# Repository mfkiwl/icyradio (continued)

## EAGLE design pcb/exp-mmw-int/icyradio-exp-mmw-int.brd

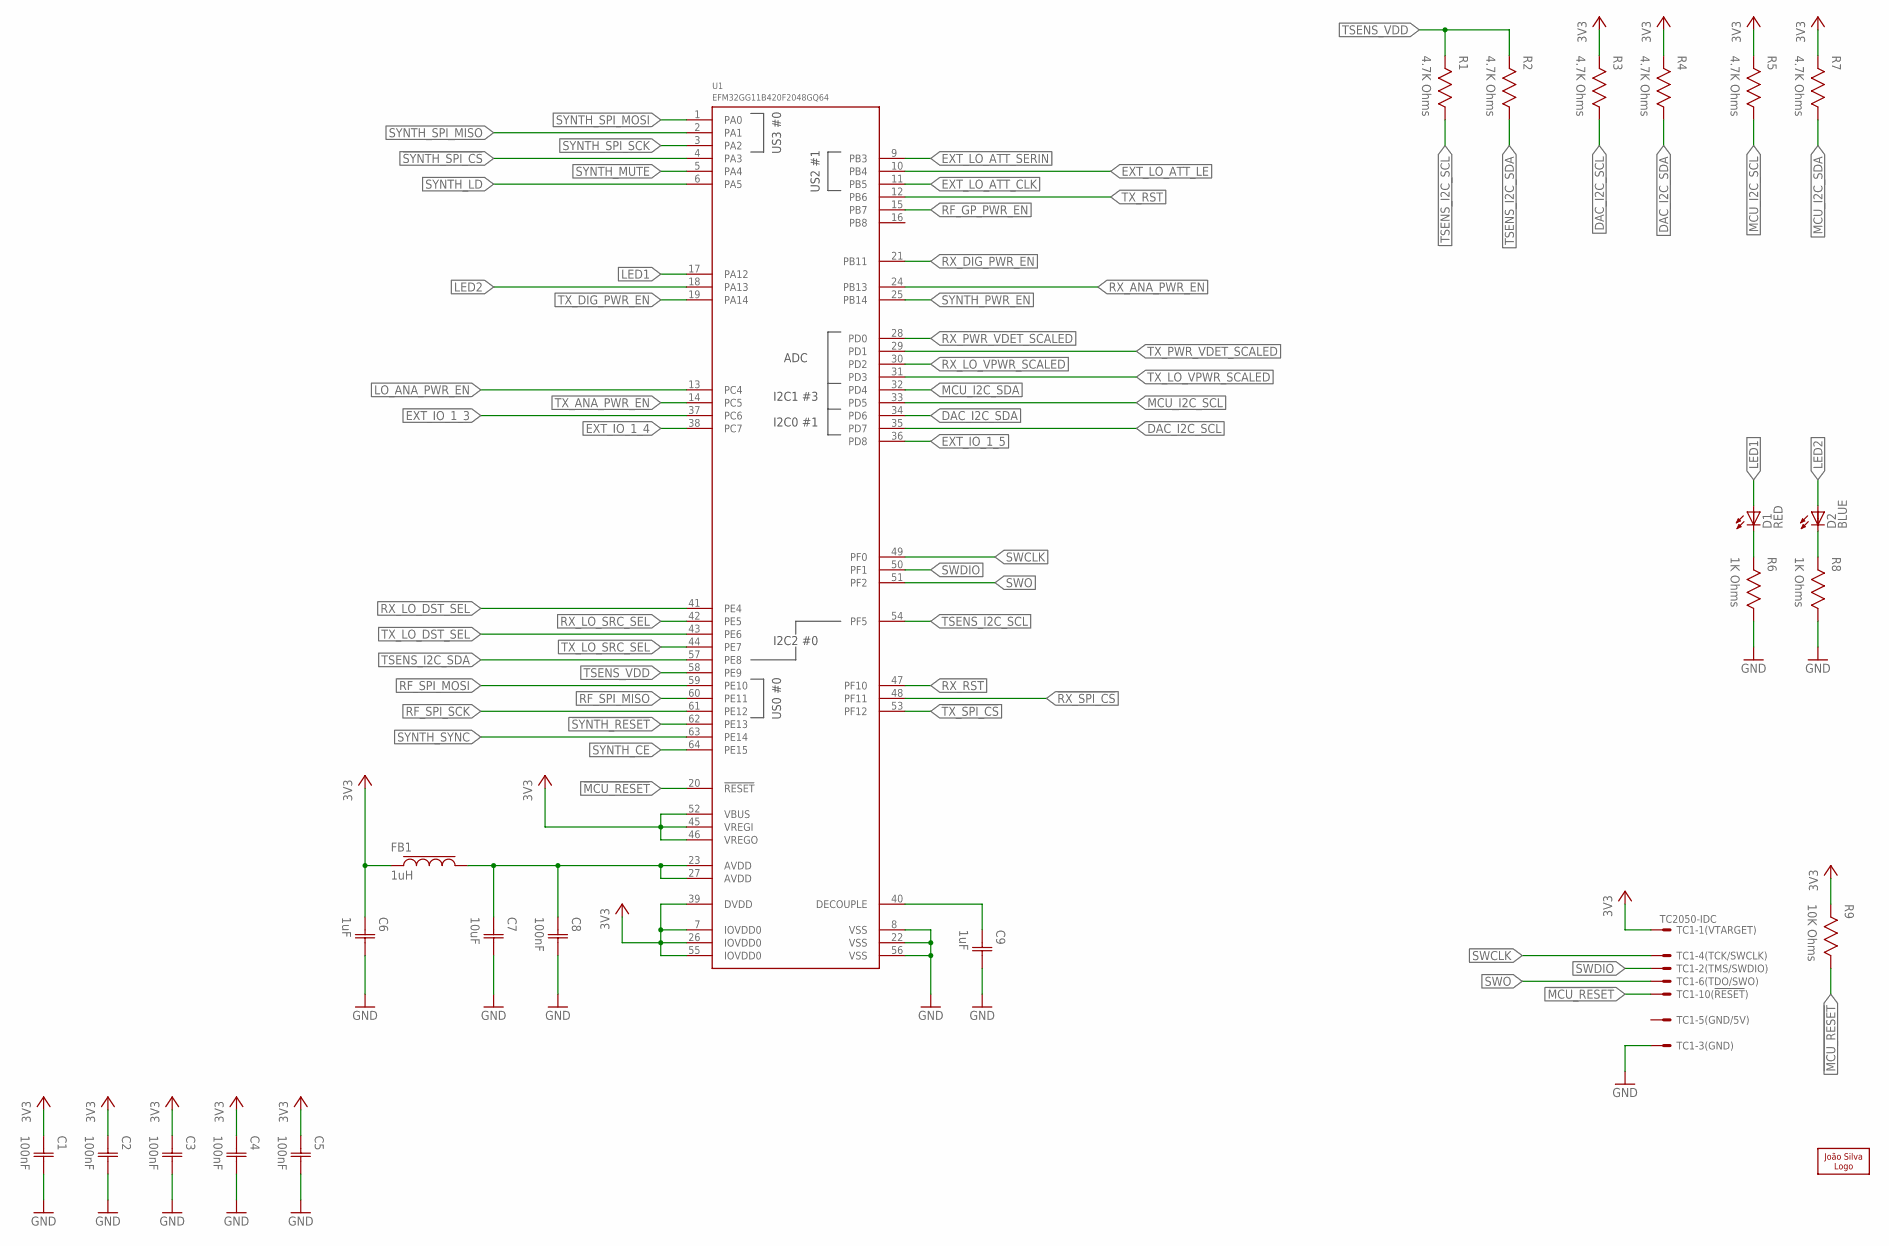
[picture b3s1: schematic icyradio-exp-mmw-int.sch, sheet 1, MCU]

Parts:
C1, C2, C3, C4, C5, C8: 100nF; CAP0402
C6, C9: 1uF; CAP0402
C7: 10uF; CAP0402
D1, D2: LED0603; 0603
FB1: 1uH; IND0603
LOGO1: JSILVA-5MM; JSILVA_5MM
R1, R2, R3, R4, R5, R7: 4.7K Ohms; RES0402
R6, R8: 1K Ohms; RES0402
R9: 10K Ohms; RES0402
TC1: TC2050-IDC
U1: EFM32GG11B420F2048GQ64; QFP64

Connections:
3V3: C1.1 (C1), C2.1 (C1), C3.1 (C1), C4.1 (C1), C5.1 (C1), C6.1 (C1), FB1.1, R3.2, R4.2, R5.2, R7.2, R9.2, TC1.1, U1.7 (IOVDD0), U1.26 (IOVDD0), U1.39 (DVDD), U1.45 (VREGI), U1.46 (VREGO), U1.52 (VBUS), U1.55 (IOVDD0); also elsewhere on the board
!MCU_RESET: R9.1, TC1.10, U1.20 (!RESET)
!RX_SPI_CS: U1.48 (PF11); also elsewhere on the board
!SYNTH_RESET: U1.62 (PE13); also elsewhere on the board
!SYNTH_SPI_CS: U1.4 (PA3); also elsewhere on the board
!TX_SPI_CS: U1.53 (PF12); also elsewhere on the board
DAC_I2C_SCL: R3.1, U1.35 (PD7); also elsewhere on the board
DAC_I2C_SDA: R4.1, U1.34 (PD6); also elsewhere on the board
EXT_IO_1_3: U1.37 (PC6); also elsewhere on the board
EXT_IO_1_4: U1.38 (PC7); also elsewhere on the board
EXT_IO_1_5: U1.36 (PD8); also elsewhere on the board
EXT_LO_ATT_CLK: U1.11 (PB5); also elsewhere on the board
EXT_LO_ATT_LE: U1.10 (PB4); also elsewhere on the board
EXT_LO_ATT_SERIN: U1.9 (PB3); also elsewhere on the board
GND: C1.2 (C2), C2.2 (C2), C3.2 (C2), C4.2 (C2), C5.2 (C2), C6.2 (C2), C7.2 (C2), C8.2 (C2), C9.2 (C2), R6.1, R8.1, TC1.3, U1.8 (VSS), U1.22 (VSS), U1.56 (VSS); also elsewhere on the board
LED1: D1.A, U1.17 (PA12)
LED2: D2.A, U1.18 (PA13)
LO_ANA_PWR_EN: U1.13 (PC4); also elsewhere on the board
MCU_AVDD: C7.1 (C1), C8.1 (C1), FB1.2, U1.23 (AVDD), U1.27 (AVDD)
MCU_I2C_SCL: R5.1, U1.33 (PD5); also elsewhere on the board
MCU_I2C_SDA: R7.1, U1.32 (PD4); also elsewhere on the board
unnamed: C9.1 (C1), U1.40 (DECOUPLE)
unnamed: D1.C, R6.2
unnamed: D2.C, R8.2
RF_GP_PWR_EN: U1.15 (PB7); also elsewhere on the board
RF_SPI_MISO: U1.60 (PE11); also elsewhere on the board
RF_SPI_MOSI: U1.59 (PE10); also elsewhere on the board
RF_SPI_SCK: U1.61 (PE12); also elsewhere on the board
RX_ANA_PWR_EN: U1.24 (PB13); also elsewhere on the board
RX_DIG_PWR_EN: U1.21 (PB11); also elsewhere on the board
RX_LO_DST_SEL: U1.41 (PE4); also elsewhere on the board
RX_LO_SRC_SEL: U1.42 (PE5); also elsewhere on the board
RX_LO_VPWR_SCALED: U1.30 (PD2); also elsewhere on the board
RX_PWR_VDET_SCALED: U1.28 (PD0); also elsewhere on the board
RX_RST: U1.47 (PF10); also elsewhere on the board
SWCLK: TC1.4, U1.49 (PF0)
SWDIO: TC1.2, U1.50 (PF1)
SWO: TC1.6, U1.51 (PF2)
SYNTH_CE: U1.64 (PE15); also elsewhere on the board
SYNTH_LD: U1.6 (PA5); also elsewhere on the board
SYNTH_MUTE: U1.5 (PA4); also elsewhere on the board
SYNTH_PWR_EN: U1.25 (PB14); also elsewhere on the board
SYNTH_SPI_MISO: U1.2 (PA1); also elsewhere on the board
SYNTH_SPI_MOSI: U1.1 (PA0); also elsewhere on the board
SYNTH_SPI_SCK: U1.3 (PA2); also elsewhere on the board
SYNTH_SYNC: U1.63 (PE14); also elsewhere on the board
TSENS_I2C_SCL: R1.1, U1.54 (PF5); also elsewhere on the board
TSENS_I2C_SDA: R2.1, U1.57 (PE8); also elsewhere on the board
TSENS_VDD: R1.2, R2.2, U1.58 (PE9); also elsewhere on the board
TX_ANA_PWR_EN: U1.14 (PC5); also elsewhere on the board
TX_DIG_PWR_EN: U1.19 (PA14); also elsewhere on the board
TX_LO_DST_SEL: U1.43 (PE6); also elsewhere on the board
TX_LO_SRC_SEL: U1.44 (PE7); also elsewhere on the board
TX_LO_VPWR_SCALED: U1.31 (PD3); also elsewhere on the board
TX_PWR_VDET_SCALED: U1.29 (PD1); also elsewhere on the board
TX_RST: U1.12 (PB6); also elsewhere on the board

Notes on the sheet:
US0 #0
I2C1 #3
US3 #0
I2C2 #0
US2 #1
I2C0 #1
ADC

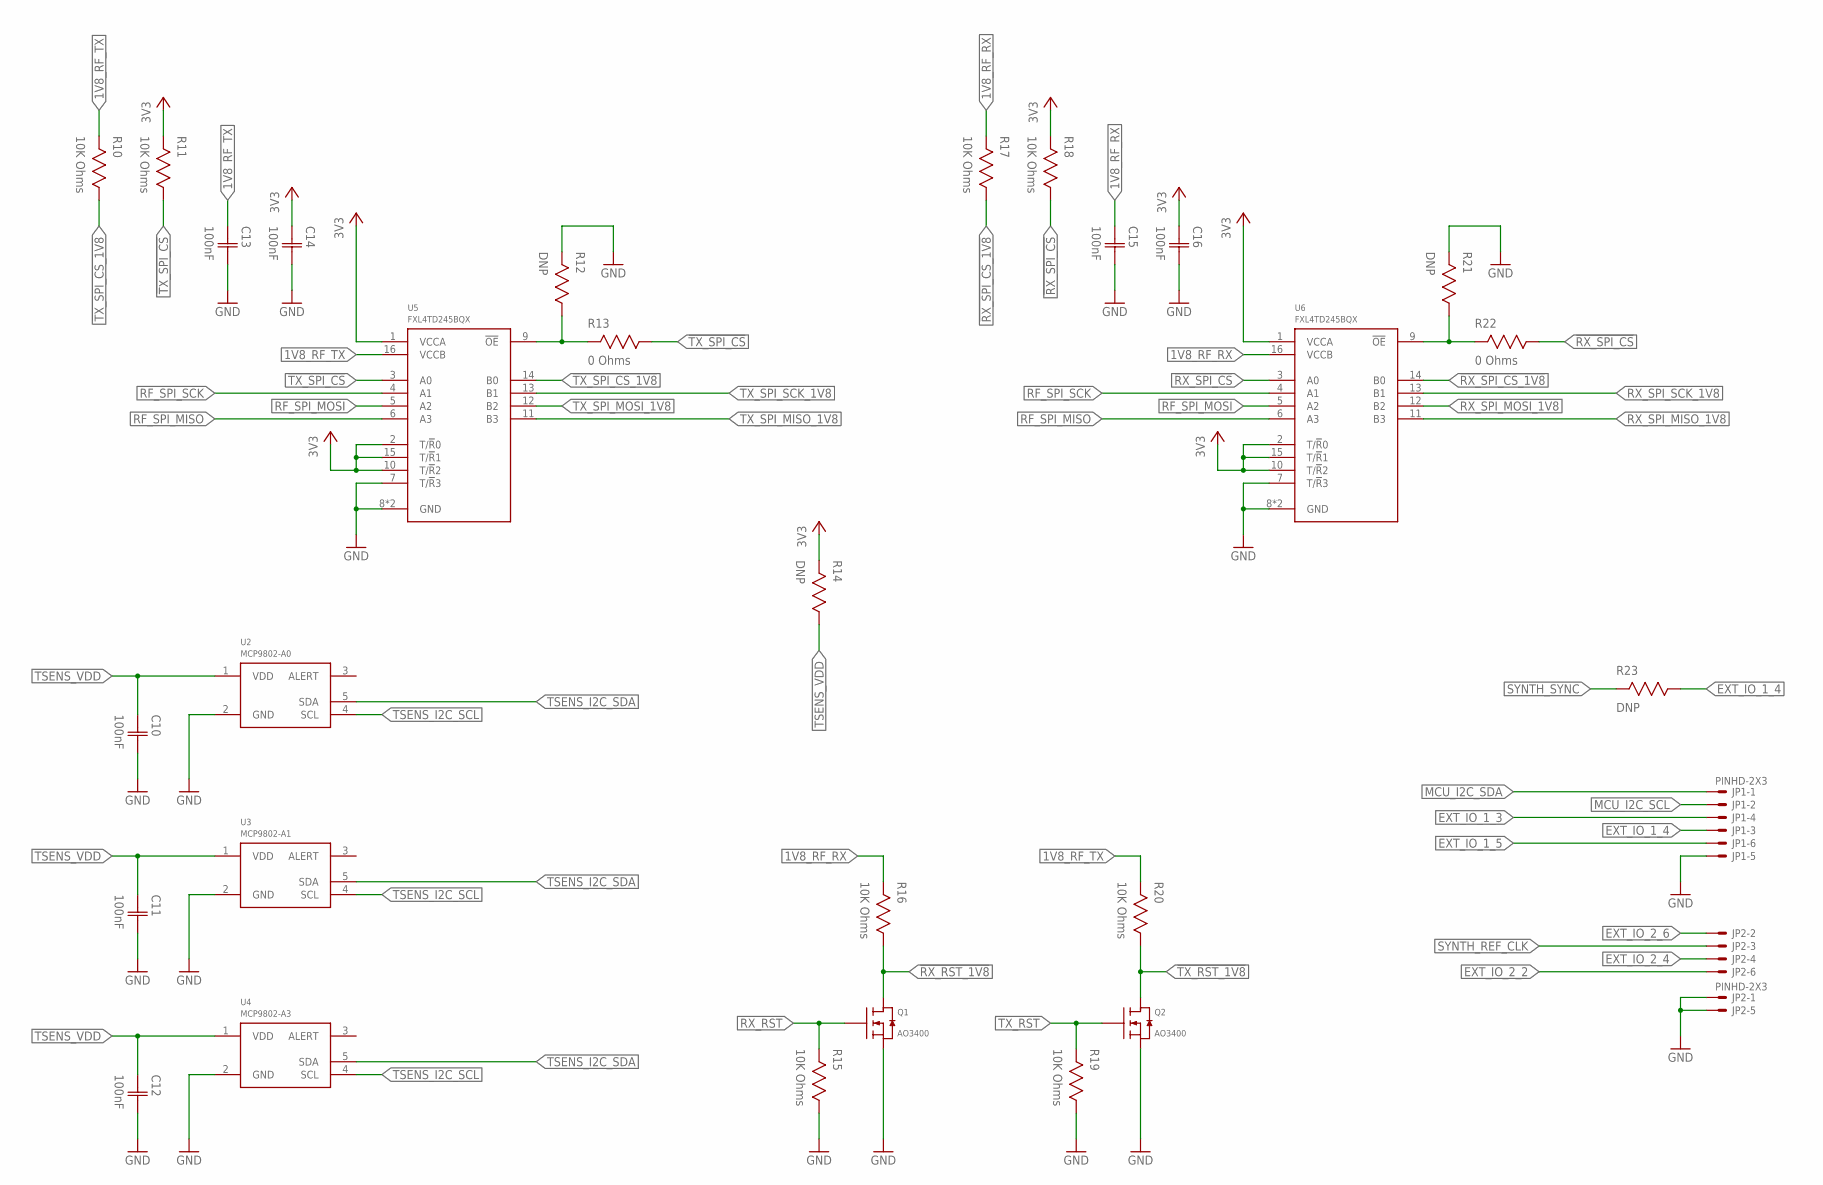
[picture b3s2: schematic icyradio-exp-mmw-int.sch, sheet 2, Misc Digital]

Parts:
C10, C11, C12, C13, C14, C15, C16: 100nF; CAP0402
JP1, JP2: PINHD-2X3; 2X03
Q1, Q2: AO3400; SOT23
R10, R11, R15, R16, R17, R18, R19, R20: 10K Ohms; RES0402
R12, R14, R21, R23: DNP; RES0402
R13, R22: 0 Ohms; RES0402
U2: MCP9802-A0; SOT23-5
U3: MCP9802-A1; SOT23-5
U4: MCP9802-A3; SOT23-5
U5, U6: FXL4TD245BQX; DQFN16

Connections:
1V8_RF_RX: C15.1 (C1), R16.2, R17.2, U6.16 (VCCB); also elsewhere on the board
1V8_RF_TX: C13.1 (C1), R10.2, R20.2, U5.16 (VCCB); also elsewhere on the board
3V3: C14.1 (C1), C16.1 (C1), R11.2, R14.2, R18.2, U5.1 (VCCA), U5.2 (T/!R!0), U5.10 (T/!R!2), U5.15 (T/!R!1), U6.1 (VCCA), U6.2 (T/!R!0), U6.10 (T/!R!2), U6.15 (T/!R!1); also elsewhere on the board
!RX_RST_1V8: Q1.3 (D), R16.1; also elsewhere on the board
!RX_SPI_CS: R18.1, R22.1, U6.3 (A0); also elsewhere on the board
!RX_SPI_CS_1V8: R17.1, U6.14 (B0); also elsewhere on the board
!RX_SPI_OE: R21.1, R22.2, U6.9 (!OE)
!TX_RST_1V8: Q2.3 (D), R20.1; also elsewhere on the board
!TX_SPI_CS: R11.1, R13.1, U5.3 (A0); also elsewhere on the board
!TX_SPI_CS_1V8: R10.1, U5.14 (B0); also elsewhere on the board
!TX_SPI_OE: R12.1, R13.2, U5.9 (!OE)
EXT_IO_1_3: JP1.4; also elsewhere on the board
EXT_IO_1_4: JP1.3, R23.1; also elsewhere on the board
EXT_IO_1_5: JP1.6; also elsewhere on the board
EXT_IO_2_2: JP2.6
EXT_IO_2_4: JP2.4
EXT_IO_2_6: JP2.2
GND: C10.2 (C2), C11.2 (C2), C12.2 (C2), C13.2 (C2), C14.2 (C2), C15.2 (C2), C16.2 (C2), JP1.5, JP2.1, JP2.5, Q1.2 (S), Q2.2 (S), R12.2, R15.1, R19.1, R21.2, U2.2 (GND), U3.2 (GND), U4.2 (GND), U5.7 (T/!R!3), U5.8 (GND), U5.17 (GND), U6.7 (T/!R!3), U6.8 (GND), U6.17 (GND); also elsewhere on the board
MCU_I2C_SCL: JP1.2; also elsewhere on the board
MCU_I2C_SDA: JP1.1; also elsewhere on the board
RF_SPI_MISO: U5.6 (A3), U6.6 (A3); also elsewhere on the board
RF_SPI_MOSI: U5.5 (A2), U6.5 (A2); also elsewhere on the board
RF_SPI_SCK: U5.4 (A1), U6.4 (A1); also elsewhere on the board
RX_RST: Q1.1 (G), R15.2; also elsewhere on the board
RX_SPI_MISO_1V8: U6.11 (B3); also elsewhere on the board
RX_SPI_MOSI_1V8: U6.12 (B2); also elsewhere on the board
RX_SPI_SCK_1V8: U6.13 (B1); also elsewhere on the board
SYNTH_REF_CLK: JP2.3; also elsewhere on the board
SYNTH_SYNC: R23.2; also elsewhere on the board
TSENS_I2C_SCL: U2.4 (SCL), U3.4 (SCL), U4.4 (SCL); also elsewhere on the board
TSENS_I2C_SDA: U2.5 (SDA), U3.5 (SDA), U4.5 (SDA); also elsewhere on the board
TSENS_VDD: C10.1 (C1), C11.1 (C1), C12.1 (C1), R14.1, U2.1 (VDD), U3.1 (VDD), U4.1 (VDD); also elsewhere on the board
TX_RST: Q2.1 (G), R19.2; also elsewhere on the board
TX_SPI_MISO_1V8: U5.11 (B3); also elsewhere on the board
TX_SPI_MOSI_1V8: U5.12 (B2); also elsewhere on the board
TX_SPI_SCK_1V8: U5.13 (B1); also elsewhere on the board

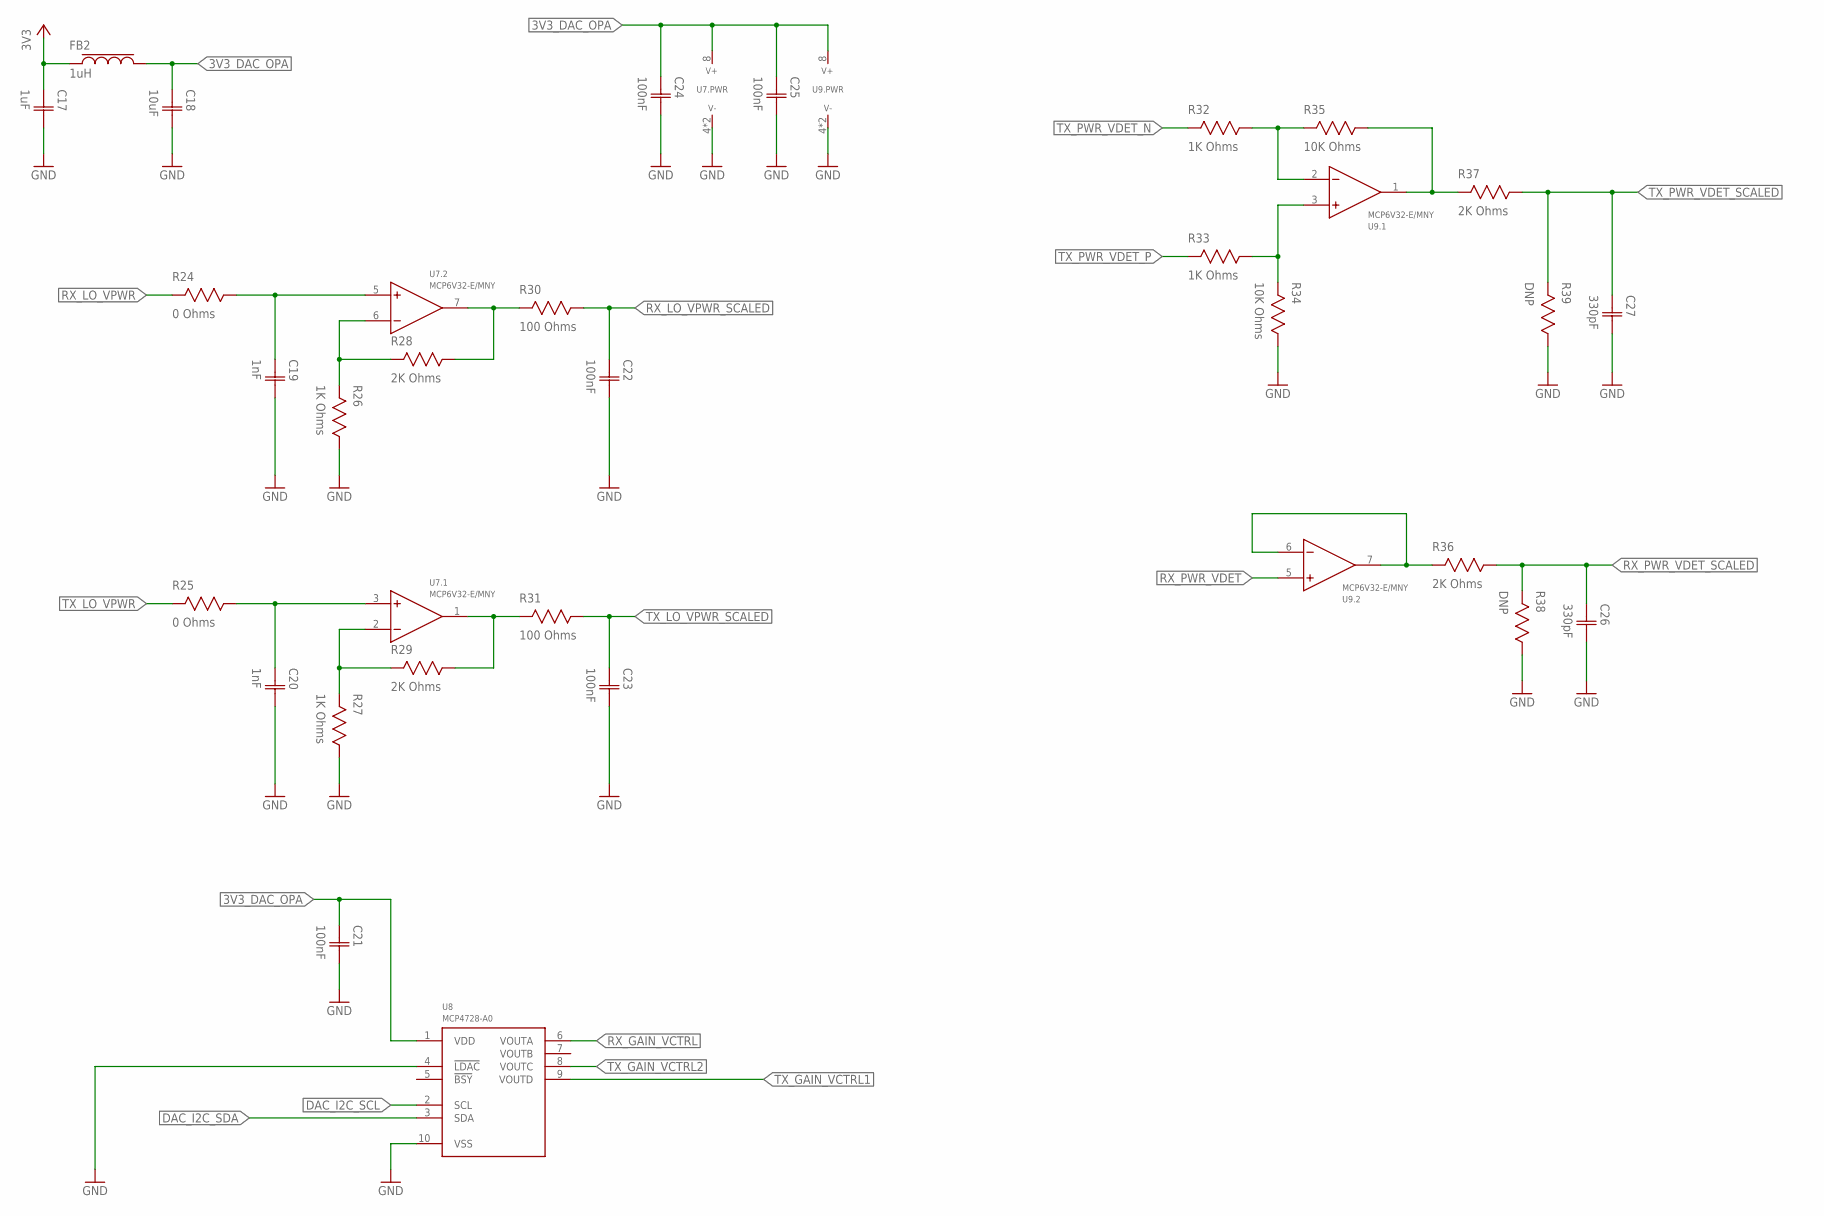
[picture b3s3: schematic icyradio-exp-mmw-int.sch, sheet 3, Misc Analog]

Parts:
C17: 1uF; CAP0402
C18: 10uF; CAP0402
C19, C20: 1nF; CAP0402
C21, C22, C23, C24, C25: 100nF; CAP0402
C26, C27: 330pF; CAP0402
FB2: 1uH; IND0603
R24, R25: 0 Ohms; RES0402
R26, R27, R32, R33: 1K Ohms; RES0402
R28, R29, R36, R37: 2K Ohms; RES0402
R30, R31: 100 Ohms; RES0402
R34, R35: 10K Ohms; RES0402
R38, R39: DNP; RES0402
U7, U9: MCP6V32-E/MNY; TDFN8
U8: MCP4728-A0; MSOP10

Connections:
3V3: C17.1 (C1), FB2.1; also elsewhere on the board
3V3_DAC_OPA: C18.1 (C1), C21.1 (C1), C24.1 (C1), C25.1 (C1), FB2.2, U7.8 (V+), U8.1 (VDD), U9.8 (V+)
DAC_I2C_SCL: U8.2 (SCL); also elsewhere on the board
DAC_I2C_SDA: U8.3 (SDA); also elsewhere on the board
GND: C17.2 (C2), C18.2 (C2), C19.2 (C2), C20.2 (C2), C21.2 (C2), C22.2 (C2), C23.2 (C2), C24.2 (C2), C25.2 (C2), C26.2 (C2), C27.2 (C2), R26.1, R27.1, R34.1, R38.1, R39.1, U7.4 (V-), U7.9 (V-), U8.4 (!LDAC), U8.10 (VSS), U9.4 (V-), U9.9 (V-); also elsewhere on the board
unnamed: R32.1, R35.2, U9.2 (-IN)
unnamed: R33.1, R34.2, U9.3 (+IN)
unnamed: R36.2, U9.6 (-IN), U9.7 (OUT)
RX_GAIN_VCTRL: U8.6 (VOUTA); also elsewhere on the board
RX_LO_VPWR: R24.2; also elsewhere on the board
RX_LO_VPWR_AMP: R28.1, R30.2, U7.7 (OUT)
RX_LO_VPWR_FB: R26.2, R28.2, U7.6 (-IN)
RX_LO_VPWR_FLT: C19.1 (C1), R24.1, U7.5 (+IN)
RX_LO_VPWR_SCALED: C22.1 (C1), R30.1; also elsewhere on the board
RX_PWR_VDET: U9.5 (+IN); also elsewhere on the board
RX_PWR_VDET_SCALED: C26.1 (C1), R36.1, R38.2; also elsewhere on the board
TX_GAIN_VCTRL1: U8.9 (VOUTD); also elsewhere on the board
TX_GAIN_VCTRL2: U8.8 (VOUTC); also elsewhere on the board
TX_LO_VPWR: R25.2; also elsewhere on the board
TX_LO_VPWR_AMP: R29.1, R31.2, U7.1 (OUT)
TX_LO_VPWR_FB: R27.2, R29.2, U7.2 (-IN)
TX_LO_VPWR_FLT: C20.1 (C1), R25.1, U7.3 (+IN)
TX_LO_VPWR_SCALED: C23.1 (C1), R31.1; also elsewhere on the board
TX_PWR_VDET: R35.1, R37.2, U9.1 (OUT)
TX_PWR_VDET_N: R32.2; also elsewhere on the board
TX_PWR_VDET_P: R33.2; also elsewhere on the board
TX_PWR_VDET_SCALED: C27.1 (C1), R37.1, R39.2; also elsewhere on the board

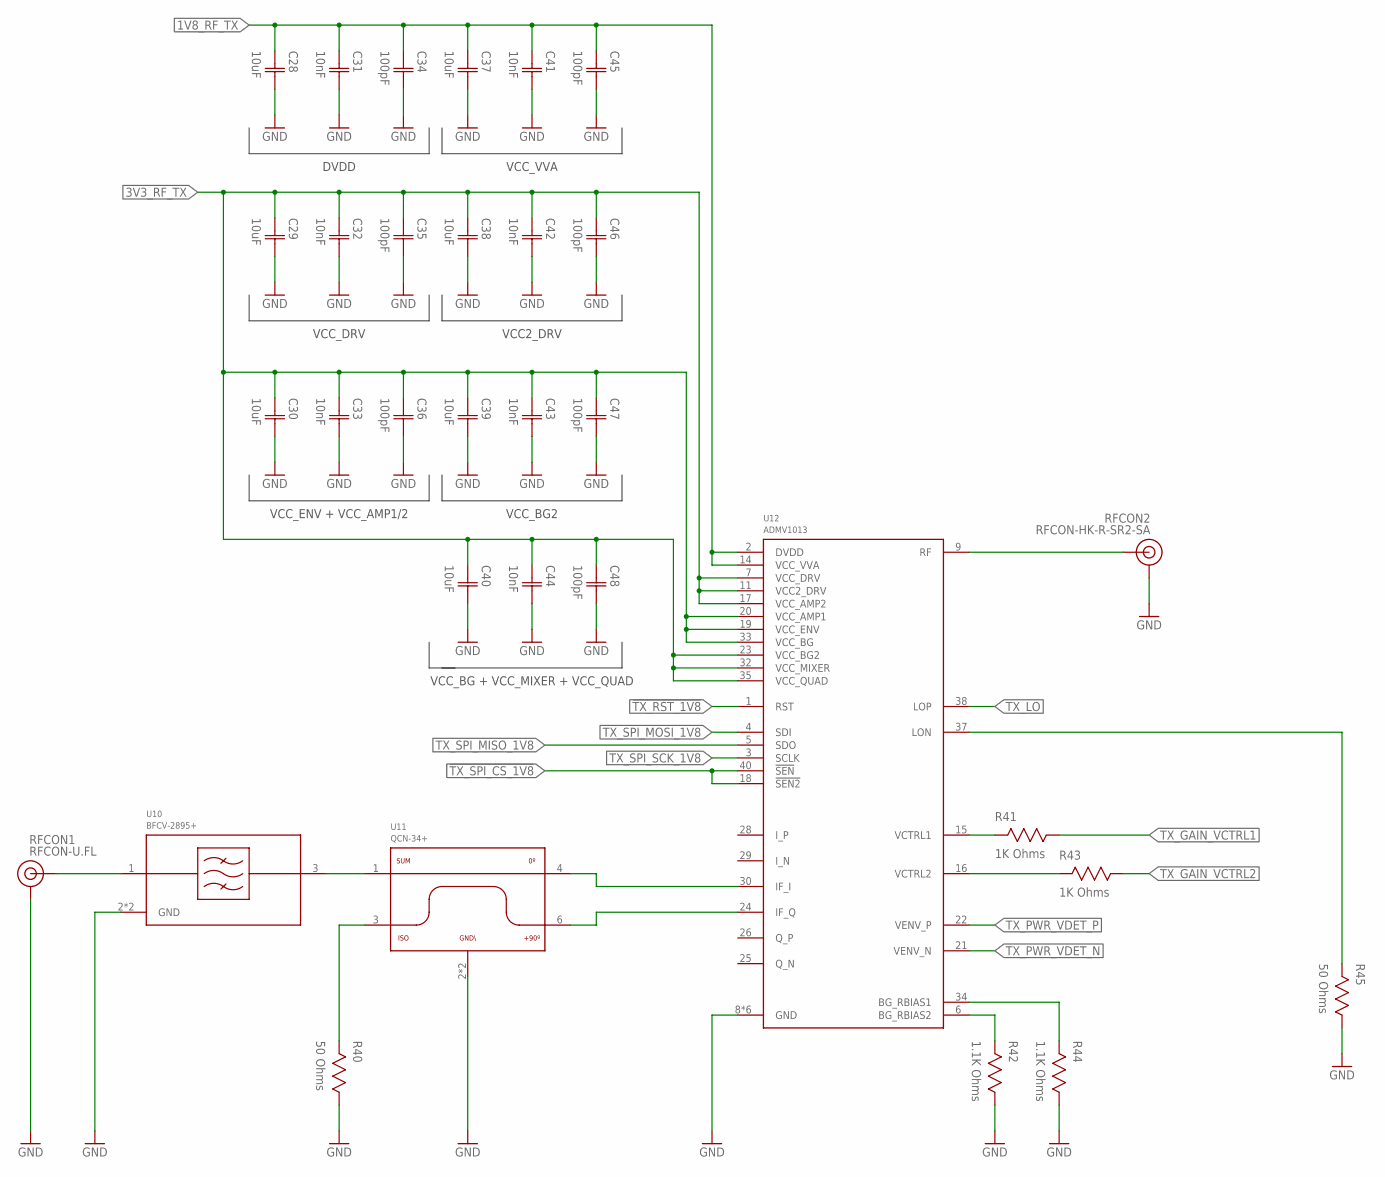
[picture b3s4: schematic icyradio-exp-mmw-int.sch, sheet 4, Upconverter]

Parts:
C28, C29, C30, C37, C38, C39, C40: 10uF; CAP0402
C31, C32, C33, C41, C42, C43, C44: 10nF; CAP0402
C34, C35, C36, C45, C46, C47, C48: 100pF; CAP0402
R40, R45: 50 Ohms; RES0402
R41, R43: 1K Ohms; RES0402
R42, R44: 1.1K Ohms; RES0402
RFCON1: RFCON-U.FL; U.FL
RFCON2: RFCON-HK-R-SR2-SA; HK-R-SR2-SA
U10: BFCV-2895+; JV1210C
U11: QCN-34+; FV1206-1
U12: ADMV1013; LGA40

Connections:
1V8_RF_TX: C28.1 (C1), C31.1 (C1), C34.1 (C1), C37.1 (C1), C41.1 (C1), C45.1 (C1), U12.2 (DVDD), U12.14 (VCC_VVA); also elsewhere on the board
3V3_RF_TX: C29.1 (C1), C30.1 (C1), C32.1 (C1), C33.1 (C1), C35.1 (C1), C36.1 (C1), C38.1 (C1), C39.1 (C1), C40.1 (C1), C42.1 (C1), C43.1 (C1), C44.1 (C1), C46.1 (C1), C47.1 (C1), C48.1 (C1), U12.7 (VCC_DRV), U12.11 (VCC2_DRV), U12.17 (VCC_AMP2), U12.19 (VCC_ENV), U12.20 (VCC_AMP1), U12.23 (VCC_BG2), U12.32 (VCC_MIXER), U12.33 (VCC_BG), U12.35 (VCC_QUAD); also elsewhere on the board
!TX_RST_1V8: U12.1 (RST); also elsewhere on the board
!TX_SPI_CS_1V8: U12.18 (!SEN2), U12.40 (!SEN); also elsewhere on the board
GND: C28.2 (C2), C29.2 (C2), C30.2 (C2), C31.2 (C2), C32.2 (C2), C33.2 (C2), C34.2 (C2), C35.2 (C2), C36.2 (C2), C37.2 (C2), C38.2 (C2), C39.2 (C2), C40.2 (C2), C41.2 (C2), C42.2 (C2), C43.2 (C2), C44.2 (C2), C45.2 (C2), C46.2 (C2), C47.2 (C2), C48.2 (C2), R40.1, R42.1, R44.1, R45.1, RFCON1.P$1 (GND), RFCON1.P$2 (GND), RFCON2.GND@1 (GND), RFCON2.GND@2 (GND), U10.2 (GND), U10.4 (GND), U11.2 (GND), U11.5 (GND), U12.8 (GND), U12.10 (GND), U12.27 (GND), U12.36 (GND), U12.39 (GND), U12.41 (GND); also elsewhere on the board
unnamed: R42.2, U12.6 (BG_RBIAS2)
unnamed: R44.2, U12.34 (BG_RBIAS1)
unnamed: R40.2, U11.3 (ISO)
unnamed: R41.2, U12.15 (VCTRL1)
unnamed: R43.2, U12.16 (VCTRL2)
TX_GAIN_VCTRL1: R41.1; also elsewhere on the board
TX_GAIN_VCTRL2: R43.1; also elsewhere on the board
TX_IF_FILT: U10.3 (RFOUT), U11.1 (SUM)
TX_IF_I: U11.4 (0DEG), U12.30 (IF_I)
TX_IF_IN: RFCON1.P$3 (SIGNAL), U10.1 (RFIN)
TX_IF_Q: U11.6 (P90DEG), U12.24 (IF_Q)
TX_LO: U12.38 (LOP); also elsewhere on the board
TX_LO_N: R45.2, U12.37 (LON)
TX_PWR_VDET_N: U12.21 (VENV_N); also elsewhere on the board
TX_PWR_VDET_P: U12.22 (VENV_P); also elsewhere on the board
TX_RF: RFCON2.SIG (SIGNAL), U12.9 (RF)
TX_SPI_MISO_1V8: U12.5 (SDO); also elsewhere on the board
TX_SPI_MOSI_1V8: U12.4 (SDI); also elsewhere on the board
TX_SPI_SCK_1V8: U12.3 (SCLK); also elsewhere on the board

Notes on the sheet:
DVDD
VCC_VVA
VCC2_DRV
VCC_DRV
VCC_BG2
VCC_ENV + VCC_AMP1/2
VCC_BG + VCC_MIXER + VCC_QUAD

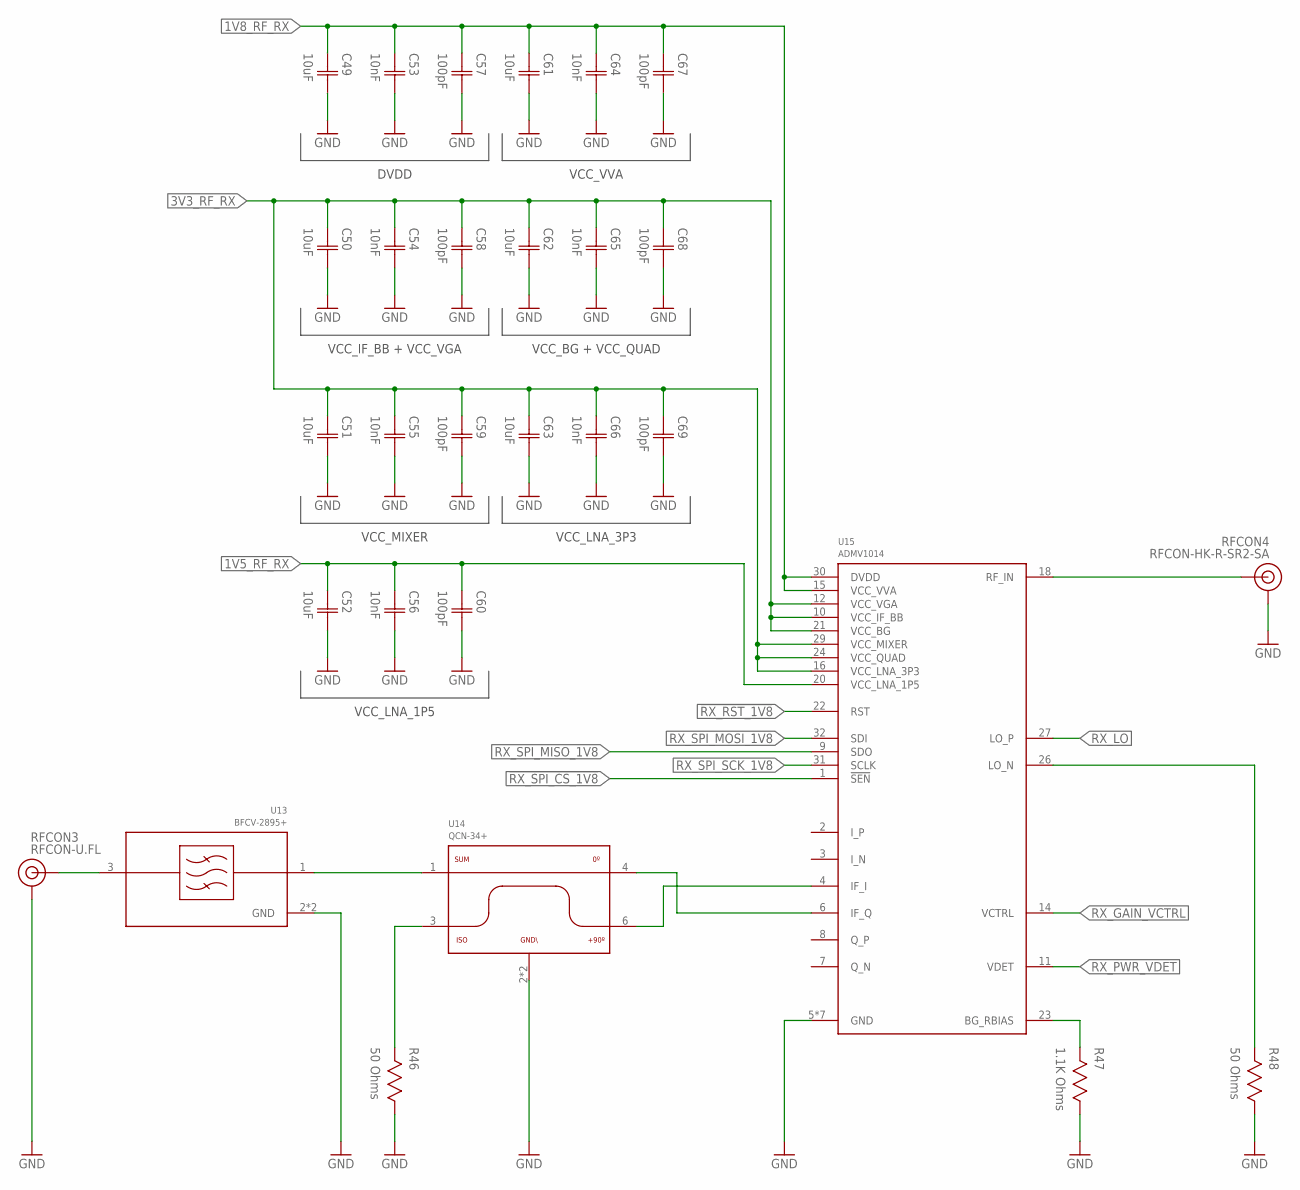
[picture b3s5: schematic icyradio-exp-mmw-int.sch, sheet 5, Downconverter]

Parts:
C49, C50, C51, C52, C61, C62, C63: 10uF; CAP0402
C53, C54, C55, C56, C64, C65, C66: 10nF; CAP0402
C57, C58, C59, C60, C67, C68, C69: 100pF; CAP0402
R46, R48: 50 Ohms; RES0402
R47: 1.1K Ohms; RES0402
RFCON3: RFCON-U.FL; U.FL
RFCON4: RFCON-HK-R-SR2-SA; HK-R-SR2-SA
U13: BFCV-2895+; JV1210C
U14: QCN-34+; FV1206-1
U15: ADMV1014; LGA32

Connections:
1V5_RF_RX: C52.1 (C1), C56.1 (C1), C60.1 (C1), U15.20 (VCC_LNA_1P5); also elsewhere on the board
1V8_RF_RX: C49.1 (C1), C53.1 (C1), C57.1 (C1), C61.1 (C1), C64.1 (C1), C67.1 (C1), U15.15 (VCC_VVA), U15.30 (DVDD); also elsewhere on the board
3V3_RF_RX: C50.1 (C1), C51.1 (C1), C54.1 (C1), C55.1 (C1), C58.1 (C1), C59.1 (C1), C62.1 (C1), C63.1 (C1), C65.1 (C1), C66.1 (C1), C68.1 (C1), C69.1 (C1), U15.10 (VCC_IF_BB), U15.12 (VCC_VGA), U15.16 (VCC_LNA_3P3), U15.21 (VCC_BG), U15.24 (VCC_QUAD), U15.29 (VCC_MIXER); also elsewhere on the board
!RX_RST_1V8: U15.22 (RST); also elsewhere on the board
!RX_SPI_CS_1V8: U15.1 (!SEN); also elsewhere on the board
GND: C49.2 (C2), C50.2 (C2), C51.2 (C2), C52.2 (C2), C53.2 (C2), C54.2 (C2), C55.2 (C2), C56.2 (C2), C57.2 (C2), C58.2 (C2), C59.2 (C2), C60.2 (C2), C61.2 (C2), C62.2 (C2), C63.2 (C2), C64.2 (C2), C65.2 (C2), C66.2 (C2), C67.2 (C2), C68.2 (C2), C69.2 (C2), R46.1, R47.1, R48.1, RFCON3.P$1 (GND), RFCON3.P$2 (GND), RFCON4.GND@1 (GND), RFCON4.GND@2 (GND), U13.2 (GND), U13.4 (GND), U14.2 (GND), U14.5 (GND), U15.5 (GND), U15.13 (GND), U15.17 (GND), U15.19 (GND), U15.25 (GND), U15.28 (GND), U15.33 (GND); also elsewhere on the board
unnamed: R47.2, U15.23 (BG_RBIAS)
unnamed: R46.2, U14.3 (ISO)
RX_GAIN_VCTRL: U15.14 (VCTRL); also elsewhere on the board
RX_IF: U13.1 (RFIN), U14.1 (SUM)
RX_IF_FILT: RFCON3.P$3 (SIGNAL), U13.3 (RFOUT)
RX_IF_I: U14.6 (P90DEG), U15.4 (IF_I)
RX_IF_Q: U14.4 (0DEG), U15.6 (IF_Q)
RX_LO: U15.27 (LO_P); also elsewhere on the board
RX_LO_N: R48.2, U15.26 (LO_N)
RX_PWR_VDET: U15.11 (VDET); also elsewhere on the board
RX_RF: RFCON4.SIG (SIGNAL), U15.18 (RF_IN)
RX_SPI_MISO_1V8: U15.9 (SDO); also elsewhere on the board
RX_SPI_MOSI_1V8: U15.32 (SDI); also elsewhere on the board
RX_SPI_SCK_1V8: U15.31 (SCLK); also elsewhere on the board

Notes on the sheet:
DVDD
VCC_VVA
VCC_BG + VCC_QUAD
VCC_IF_BB + VCC_VGA
VCC_LNA_3P3
VCC_LNA_1P5
VCC_MIXER

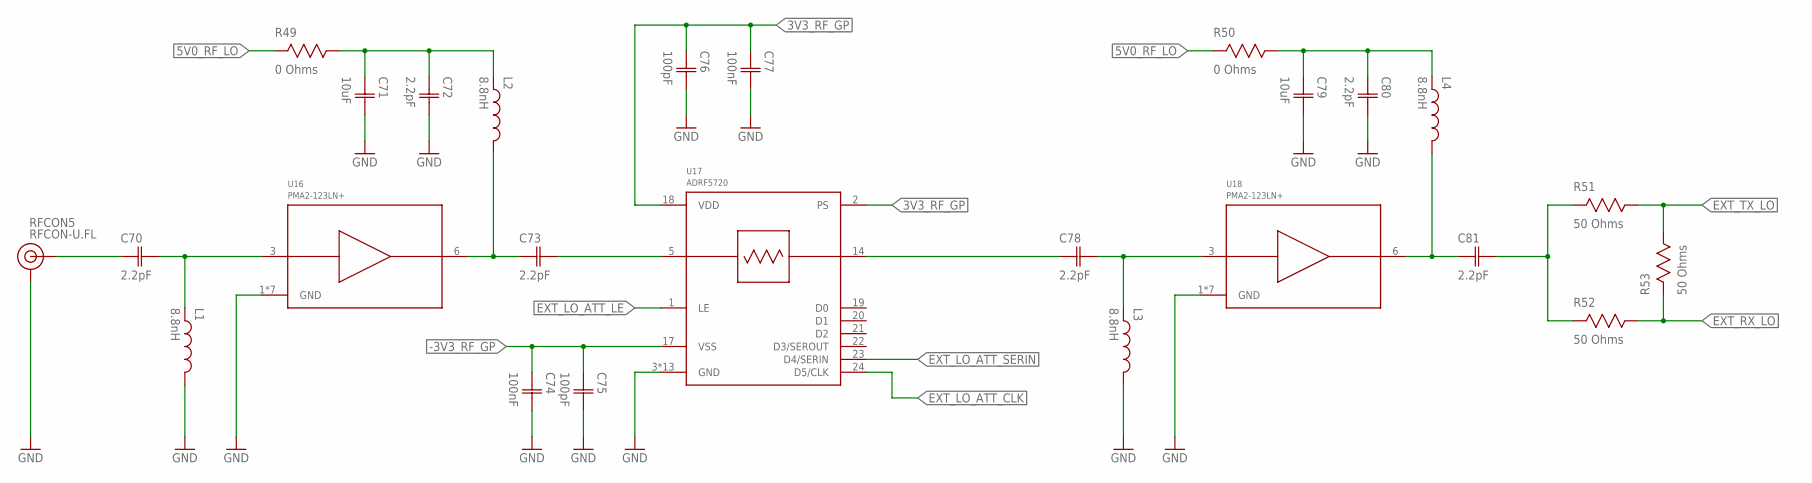
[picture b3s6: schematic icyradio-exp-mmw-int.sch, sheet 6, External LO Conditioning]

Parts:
C70, C72, C73, C78, C80, C81: 2.2pF; CAP0402
C71, C79: 10uF; CAP0402
C74, C77: 100nF; CAP0402
C75, C76: 100pF; CAP0402
L1, L2, L3, L4: 8.8nH; IND0402
R49, R50: 0 Ohms; RES0402
R51, R52, R53: 50 Ohms; RES0402
RFCON5: RFCON-U.FL; U.FL
U16, U18: PMA2-123LN+; MC1631-1
U17: ADRF5720; LGA24

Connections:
3V3_RF_GP: C76.1 (C1), C77.1 (C1), U17.2 (PS), U17.18 (VDD); also elsewhere on the board
5V0_RF_LO: R49.2, R50.2; also elsewhere on the board
-3V3_RF_GP: C74.1 (C1), C75.1 (C1), U17.17 (VSS); also elsewhere on the board
EXT_LO_AMP1_IN: C70.2 (C2), L1.1, U16.3 (RFIN)
EXT_LO_AMP1_OUT: C73.1 (C1), L2.2, U16.6 (RFOUT)
EXT_LO_AMP1_VDD: C71.1 (C1), C72.1 (C1), L2.1, R49.1
EXT_LO_AMP2_IN: C78.2 (C2), L3.1, U18.3 (RFIN)
EXT_LO_AMP2_OUT: C81.1 (C1), L4.2, U18.6 (RFOUT)
EXT_LO_AMP2_VDD: C79.1 (C1), C80.1 (C1), L4.1, R50.1
EXT_LO_ATT_CLK: U17.24 (D5/CLK); also elsewhere on the board
EXT_LO_ATT_IN: C73.2 (C2), U17.5 (ATTIN)
EXT_LO_ATT_LE: U17.1 (LE); also elsewhere on the board
EXT_LO_ATT_OUT: C78.1 (C1), U17.14 (ATTOUT)
EXT_LO_ATT_SERIN: U17.23 (D4/SERIN); also elsewhere on the board
EXT_LO_DIV_IN: C81.2 (C2), R51.2, R52.2
EXT_LO_IN: C70.1 (C1), RFCON5.P$3 (SIGNAL)
EXT_RX_LO: R52.1, R53.2; also elsewhere on the board
EXT_TX_LO: R51.1, R53.1; also elsewhere on the board
GND: C71.2 (C2), C72.2 (C2), C74.2 (C2), C75.2 (C2), C76.2 (C2), C77.2 (C2), C79.2 (C2), C80.2 (C2), L1.2, L3.2, RFCON5.P$1 (GND), RFCON5.P$2 (GND), U16.1 (GND), U16.2 (GND), U16.4 (GND), U16.5 (GND), U16.7 (GND), U16.8 (GND), U16.9 (GND), U17.3 (GND), U17.4 (GND), U17.6 (GND), U17.7 (GND), U17.8 (GND), U17.9 (GND), U17.10 (GND), U17.11 (GND), U17.12 (GND), U17.13 (GND), U17.15 (GND), U17.16 (GND), U17.25 (GND), U18.1 (GND), U18.2 (GND), U18.4 (GND), U18.5 (GND), U18.7 (GND), U18.8 (GND), U18.9 (GND); also elsewhere on the board

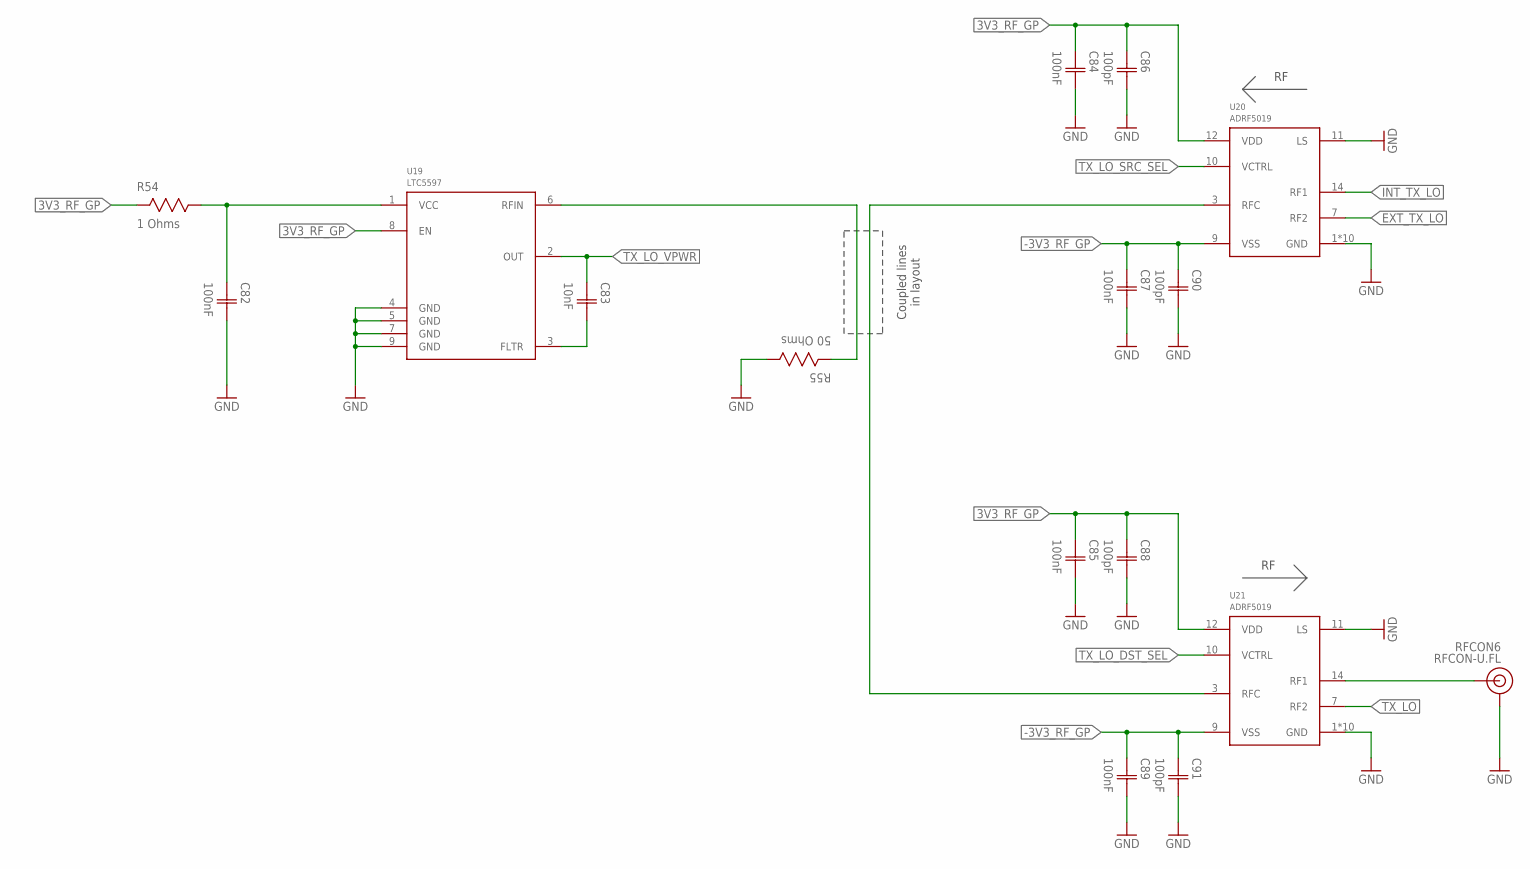
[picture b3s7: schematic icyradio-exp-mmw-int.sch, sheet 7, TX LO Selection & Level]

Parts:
C82, C84, C85, C87, C89: 100nF; CAP0402
C83: 10nF; CAP0402
C86, C88, C90, C91: 100pF; CAP0402
R54: 1 Ohms; RES0402
R55: 50 Ohms; RES0402
RFCON6: RFCON-U.FL; U.FL
U19: LTC5597; DFN8_2X2
U20, U21: ADRF5019; LFCSP16

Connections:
3V3_RF_GP: C84.1 (C1), C85.1 (C1), C86.1 (C1), C88.1 (C1), R54.2, U19.8 (EN), U20.12 (VDD), U21.12 (VDD); also elsewhere on the board
-3V3_RF_GP: C87.1 (C1), C89.1 (C1), C90.1 (C1), C91.1 (C1), U20.9 (VSS), U21.9 (VSS); also elsewhere on the board
EXT_TX_LO: U20.7 (RF2); also elsewhere on the board
GND: C82.2 (C2), C84.2 (C2), C85.2 (C2), C86.2 (C2), C87.2 (C2), C88.2 (C2), C89.2 (C2), C90.2 (C2), C91.2 (C2), R55.1, RFCON6.P$1 (GND), RFCON6.P$2 (GND), U19.4 (GND), U19.5 (GND), U19.7 (GND), U19.9 (GND), U20.1 (GND), U20.2 (GND), U20.4 (GND), U20.5 (GND), U20.6 (GND), U20.8 (GND), U20.11 (LS), U20.13 (GND), U20.15 (GND), U20.16 (GND), U20.17 (GND), U21.1 (GND), U21.2 (GND), U21.4 (GND), U21.5 (GND), U21.6 (GND), U21.8 (GND), U21.11 (LS), U21.13 (GND), U21.15 (GND), U21.16 (GND), U21.17 (GND); also elsewhere on the board
INT_TX_LO: U20.14 (RF1); also elsewhere on the board
unnamed: C83.2 (C2), U19.3 (FLTR)
unnamed: C82.1 (C1), R54.1, U19.1 (VCC)
SEL_TX_LO: U20.3 (RFC), U21.3 (RFC)
TX_LO: U21.7 (RF2); also elsewhere on the board
TX_LO_DST_SEL: U21.10 (VCTRL); also elsewhere on the board
TX_LO_MON: RFCON6.P$3 (SIGNAL), U21.14 (RF1)
TX_LO_SNS: R55.2, U19.6 (RFIN)
TX_LO_SRC_SEL: U20.10 (VCTRL); also elsewhere on the board
TX_LO_VPWR: C83.1 (C1), U19.2 (OUT); also elsewhere on the board

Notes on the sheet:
Coupled lines in layout
